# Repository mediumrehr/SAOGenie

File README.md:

# SAOGenie

The SAO Genie was inspired by the [TPM Genie](https://github.com/nccgroup/TPMGenie), specially crafted for attacking [Shitty Add-ons](https://hackaday.com/2018/06/21/this-is-the-year-conference-badges-get-their-own-badges/) at DEF CON 26. The SAO Genie was designed as a tool for electronic badge and add-on hacking, since it provides an easier interface for sniffing and manipulating data on the serial bus between a badge and targeted add-on. As electronic badges are being used more frequently in conference hacking challenges, the SAO Genie is geared to make it easier to dig into inter-badge/add-on communications.

The SAO Genie works by sitting between an electronic badge and a targeted add-on as a man-in-the-middle kind of way. The SAO Genie is able to do this by acting as a slave to the conference badge, pretending to be the targeted add-on (using the same i2c address), while also playing the role of master to the targeted add-on (forwarding and possibly manipulating) serial data packets between the badge and target add-on. The SAO Genie has both a 2x2 male header for plugging into a conference badge, and a 2x2 female header for providing a connector for the targeted add-on to connect to.

## Functionality

Currently, only monitor/passthrough mode is supported.

#### Monitor/Passthrough Mode

When placed between an electronic badge and targeted add-on, the SAO Genie will forward all communications between the type pieces of hardware, while also repeating any data out through the UART serial port.

Connect the SAO Genie as shown below:

To connect to the UART serial port, attach your serial reader to the RX, TX, and GND pins on the 'handle'.

Serial settings:

```
Baudrate: 9600
Data bits: 8
Parity: None
Stop bits: 1
```

## Installing/Updating Firmware

### Setup

Firmware can be loaded with [Atmel Studio 7.0](https://www.microchip.com/mplab/avr-support/atmel-studio-7), or install the packages below to use with your preferred text editor and compile with arm gcc.

#### arm gcc and gdb

MacOS

```
brew install armmbed/formulae/arm-none-eabi-gcc
```

#### jlink gdb server

Download install file from [segger.com](https://www.segger.com/products/debug-probes/j-link/tools/j-link-gdb-server/about-j-link-gdb-server/)

#### SWD connection

Software debug (SWD) pins are labelled on the back of the board. Connect SWDIO, SWCLK, 3V3, RESET, and GND as labelled. SWD requires the board to be powered external from the SWD port, so it's easiest to power the board from the 3V3 and GND pins on one of the SAO headers.

### Build

```
cd firmware/SAOGenie/
make -C Build/
```

### Load

#### jlink

Start jlink gdb server in one tab

```
JLinkGDBServer -if SWD -device ATSAMD21G18
```

Start gdb in another tba

```
arm-none-eabi-gdb Build/SAOGenie.elf
(gdb) target extended-remote :2331
```

Load new firmware, reset microcontroller, and run new code

```
(gdb) load
(gdb) monitor reset
(gdb) c
```

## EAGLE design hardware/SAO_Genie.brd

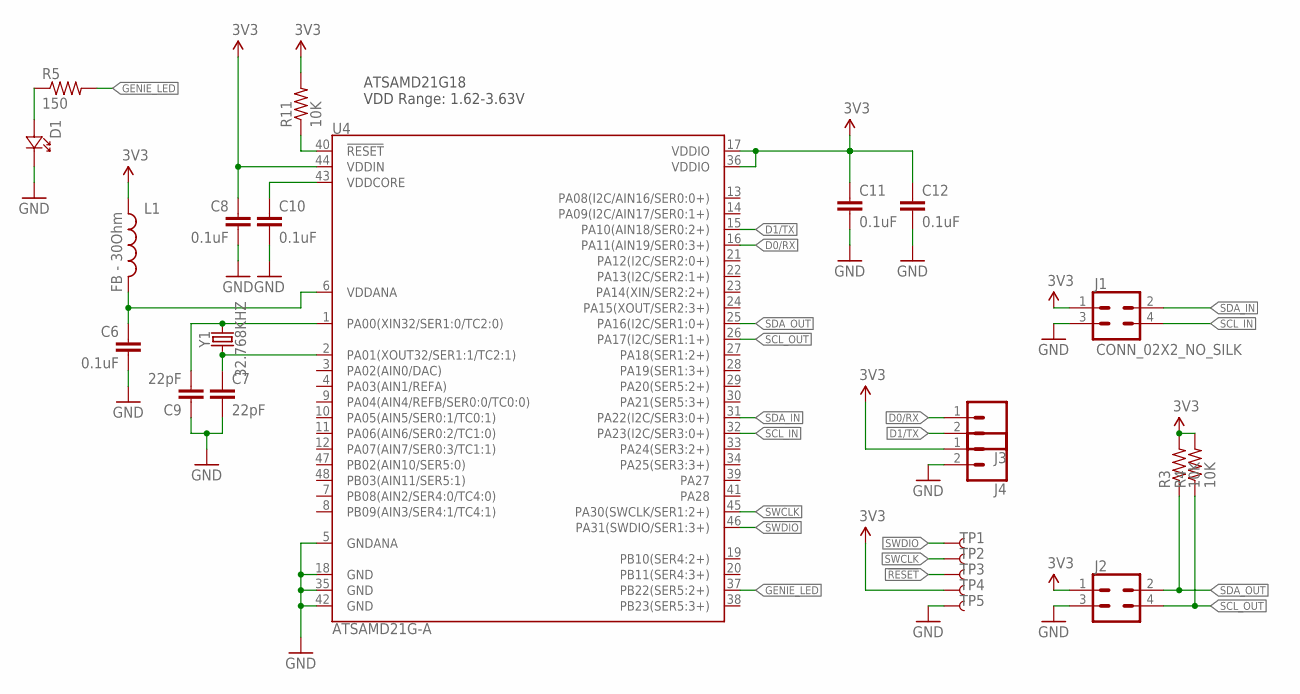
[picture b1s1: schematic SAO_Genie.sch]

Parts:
C6, C8, C10, C11, C12: 0.1uF; 0603-CAP
C7, C9: 22pF; 0603-CAP
D1: LED1206REVERSE_NO_SILK; 1206_NO_SILK
J1: CONN_02X2_NO_SILK; 2X2_NO_SILK
J2: SAO OUT; 2X2_NO_SILK
J3, J4: CONN_021X02_NO_SILK; 1X02_NO_SILK
L1: FB - 30Ohm; 0603
R3, R4, R11: 10K; 0603-RES
R5: 150; 0603-RES
TP1, TP2, TP3, TP4, TP5: TEST-POINT3X5; PAD.03X.05
U4: ATSAMD21G-A; TQFP-48
Y1: 32.768KHZ; ABS06

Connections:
3.3V: C8.1, C11.1, C12.1, J1.1, J2.1, J4.1, L1.1, R3.2, R4.2, R11.2, TP4.P$1, U4.17 (VDDIO), U4.36 (VDDIO), U4.44 (VDDIN)
!RESET: R11.1, TP3.P$1, U4.40 (!RESET!)
D0/RX: J3.1, U4.16 (PA11(AIN19/SER0:3+))
D1/TX: J3.2, U4.15 (PA10(AIN18/SER0:2+))
GENIE_LED: R5.2, U4.37 (PB22(SER5:2+))
GND: C6.2, C7.2, C8.2, C9.1, C10.2, C11.2, C12.2, D1.P$1, J1.3, J2.3, J4.2, TP5.P$1, U4.5 (GNDANA), U4.18 (GND), U4.35 (GND), U4.42 (GND)
unnamed: C7.1, U4.2 (PA01(XOUT32/SER1:1/TC2:1)), Y1.P$1 (1)
unnamed: D1.P$2, R5.1
unnamed: C9.2, U4.1 (PA00(XIN32/SER1:0/TC2:0)), Y1.P$2 (2)
SCL_IN: J1.4, U4.32 (PA23(I2C/SER3:0+))
SCL_OUT: J2.4, R4.1, U4.26 (PA17(I2C/SER1:1+))
SDA_IN: J1.2, U4.31 (PA22(I2C/SER3:0+))
SDA_OUT: J2.2, R3.1, U4.25 (PA16(I2C/SER1:0+))
SWCLK: TP2.P$1, U4.45 (PA30(SWCLK/SER1:2+))
SWDIO: TP1.P$1, U4.46 (PA31(SWDIO/SER1:3+))
VDDANA: C6.1, L1.2, U4.6 (VDDANA)
VDDCORE: C10.1, U4.43 (VDDCORE)

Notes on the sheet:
ATSAMD21G18 VDD Range: 1.62-3.63V

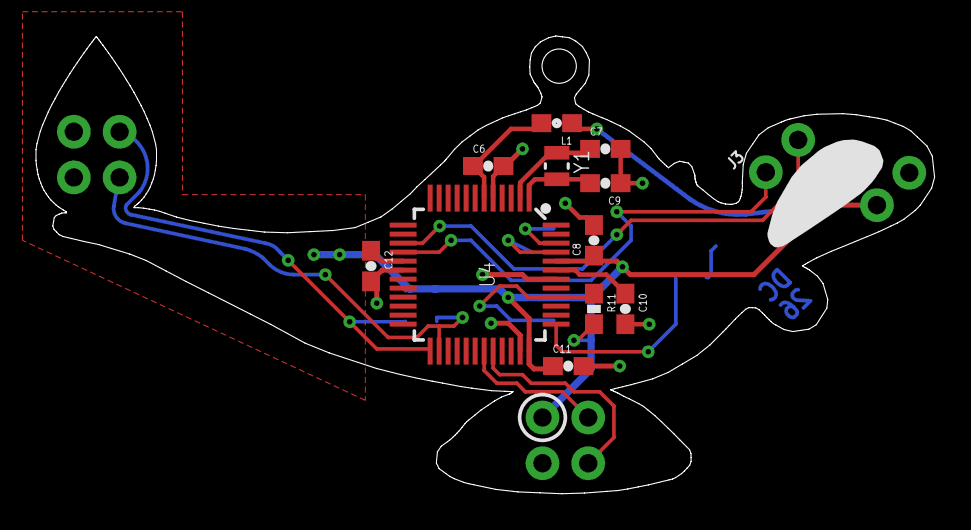
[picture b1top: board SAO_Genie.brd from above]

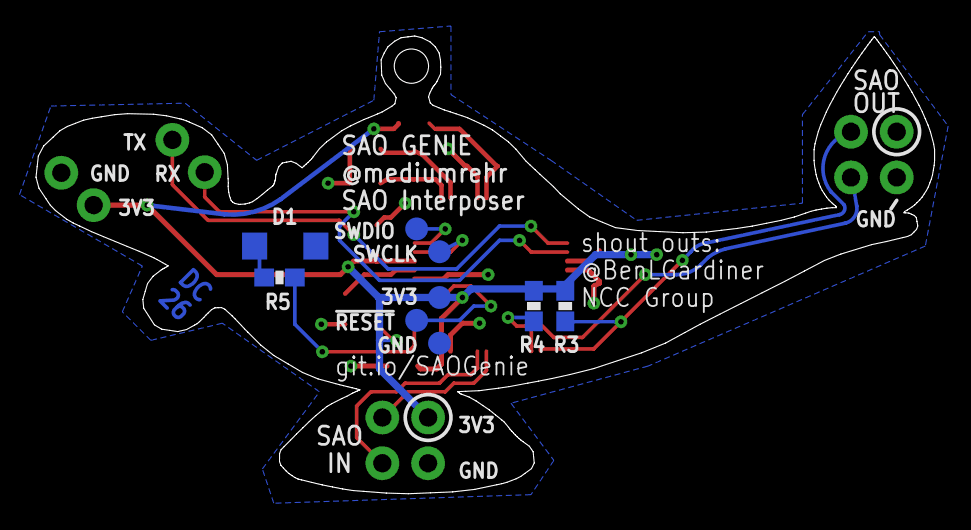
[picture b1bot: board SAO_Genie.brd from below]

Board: 2 copper layers, 49.9 x 25.4 mm, 24 parts (9 on the bottom side), 17 nets.

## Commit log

2018-07-24 add eagle design files
2019-04-30 Create LICENSE
2019-04-30 initial commit of firmware that adds ability to monitor serial communication
2019-04-30 update hardware schematic, board layout, and bill of material
2019-05-01 Remove GNU GPLv3 license
2019-05-01 add MIT license

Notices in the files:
parts and their libraries:
SparkFun-Capacitors: Licensing: Creative Commons ShareAlike 4.0 International - https://creativecommons.org/licenses/by-sa/4.0
